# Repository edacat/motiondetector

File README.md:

# motiondetector
Combined Motion Detector using Radar and PIR Sensor

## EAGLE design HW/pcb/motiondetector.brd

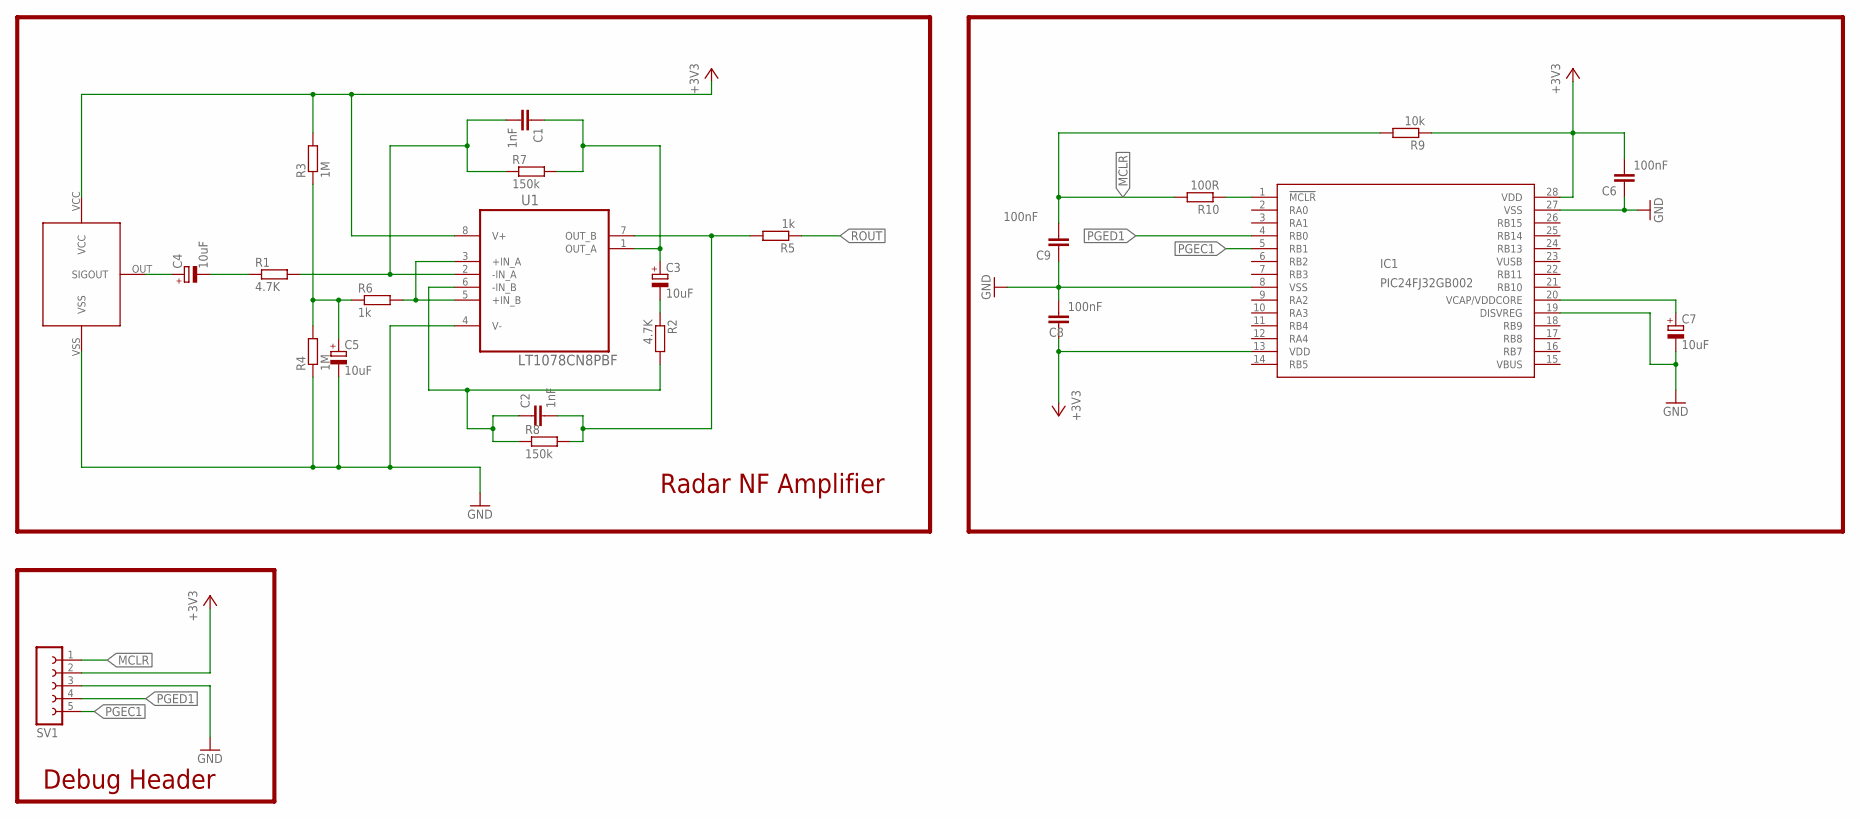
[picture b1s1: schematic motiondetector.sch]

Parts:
C1, C2: 1nF; C025-025X050
C3, C4, C5, C7: 10uF; E2,5-5
C6, C8, C9: 100nF; C025-025X050
IC1: PIC24FJ32GB002; DIL28-3
R1, R2: 4.7K; 0207/10
R3, R4: 1M; 0207/10
R5, R6: 1k; 0207/10
R7, R8: 150k; 0207/10
R9: 10k; 0207/10
R10: 100R; 0207/10
SV1: FE05-1
U1: LT1078CN8PBF; DIP254P762X393-8
U$1: RSM3650

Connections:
+3V3: C6.2, C8.1, IC1.13 (VDD), IC1.28 (VDD), R3.2, R9.1, SV1.2, U1.8 (V+), U$1.VCC
GND: C5.-, C6.1, C7.-, C8.2, C9.1, IC1.8 (VSS), IC1.19 (DISVREG), IC1.27 (VSS), R4.1, SV1.3, U1.4 (V-), U$1.VSS
MCLR: C9.2, R9.2, R10.2, SV1.1
unnamed: C4.-, R1.1
unnamed: C1.2, R1.2, R7.1, U1.2 (-IN_A)
unnamed: C4.+, U$1.OUT (SIGOUT)
unnamed: C3.-, R2.1
unnamed: R6.2, U1.3 (+IN_A), U1.5 (+IN_B)
unnamed: C5.+, R3.1, R4.2, R6.1
unnamed: C2.2, R5.2, R8.2, U1.7 (OUT_B)
unnamed: C1.1, C3.+, R7.2, U1.1 (OUT_A)
unnamed: C2.1, R2.2, R8.1, U1.6 (-IN_B)
unnamed: C7.+, IC1.20 (VCAP/VDDCORE)
unnamed: IC1.1 (!MCLR), R10.1
PGEC1: IC1.5 (RB1), SV1.5
PGED1: IC1.4 (RB0), SV1.4
ROUT: R5.1

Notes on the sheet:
Radar NF Amplifier
Debug Header

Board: 2 copper layers, 23 parts (0 on the bottom side), 16 nets, no tracks yet.

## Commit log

2015-08-18 initial
2015-08-18 pcb initial
2015-08-22 test
2015-09-06 analog stage in circuit finished and testet
2015-09-06 base PIC24F circuit added
